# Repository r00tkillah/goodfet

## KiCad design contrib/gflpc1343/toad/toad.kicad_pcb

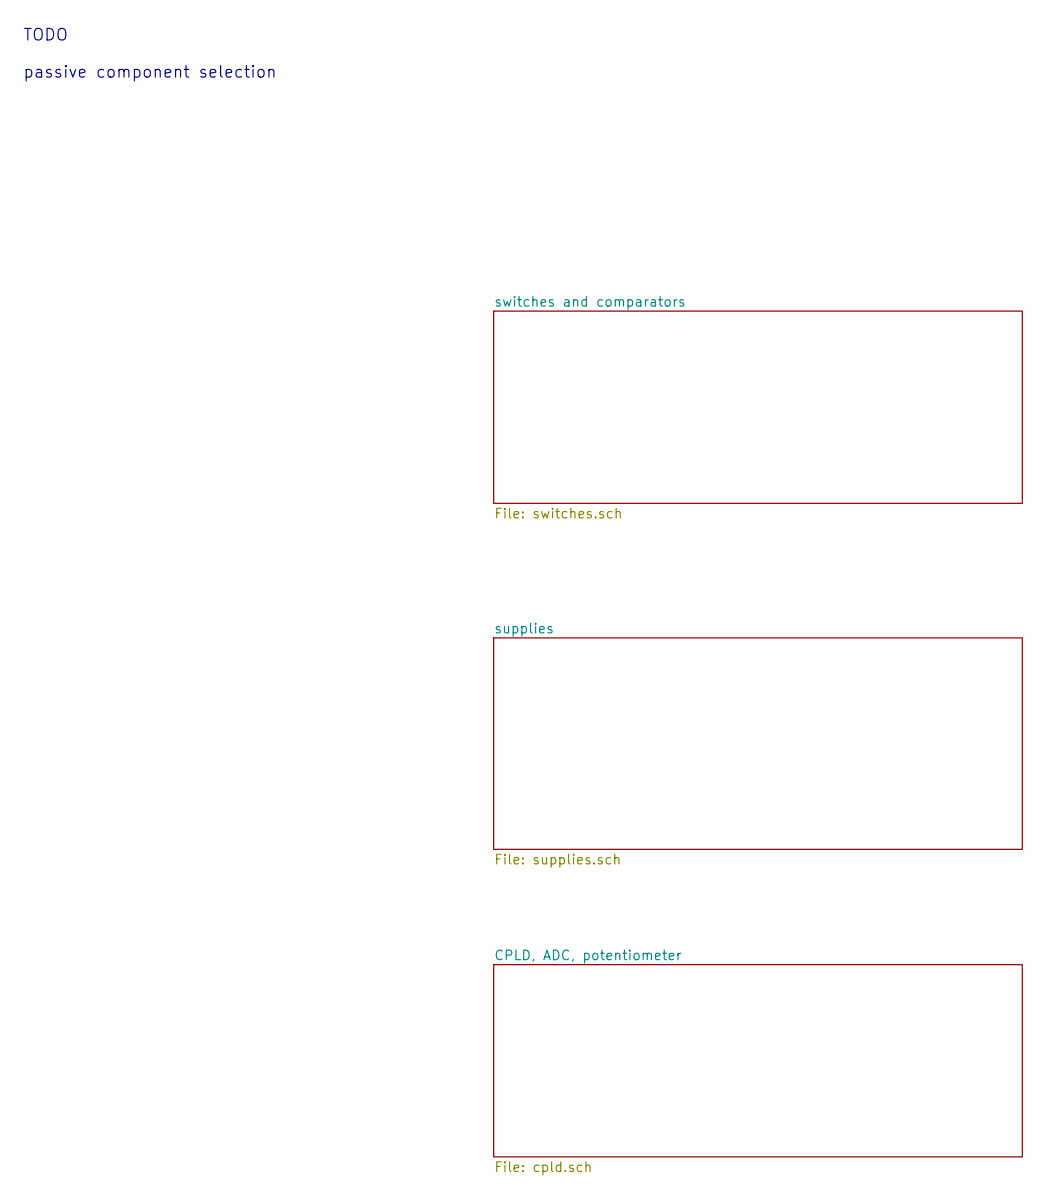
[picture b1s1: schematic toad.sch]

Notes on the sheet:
TODO passive component selection

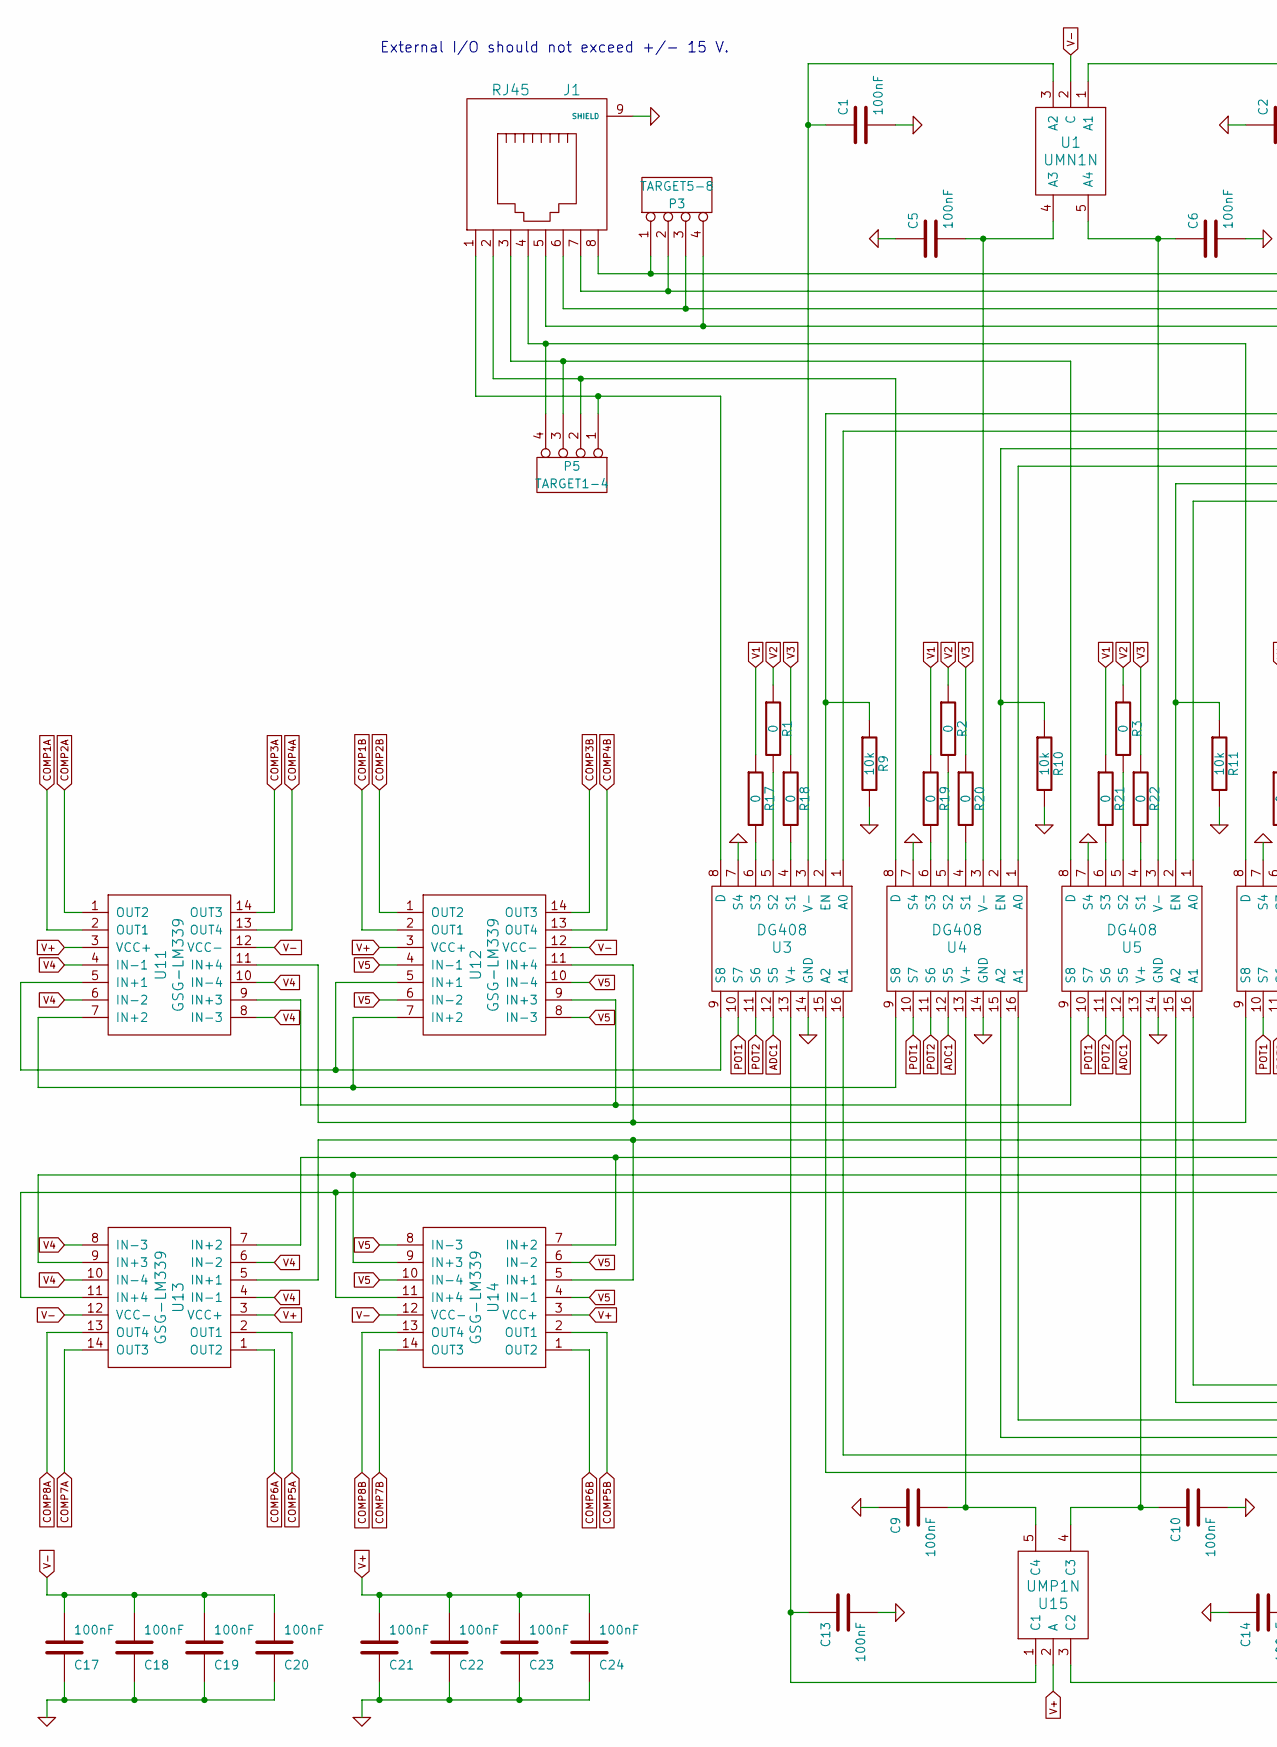
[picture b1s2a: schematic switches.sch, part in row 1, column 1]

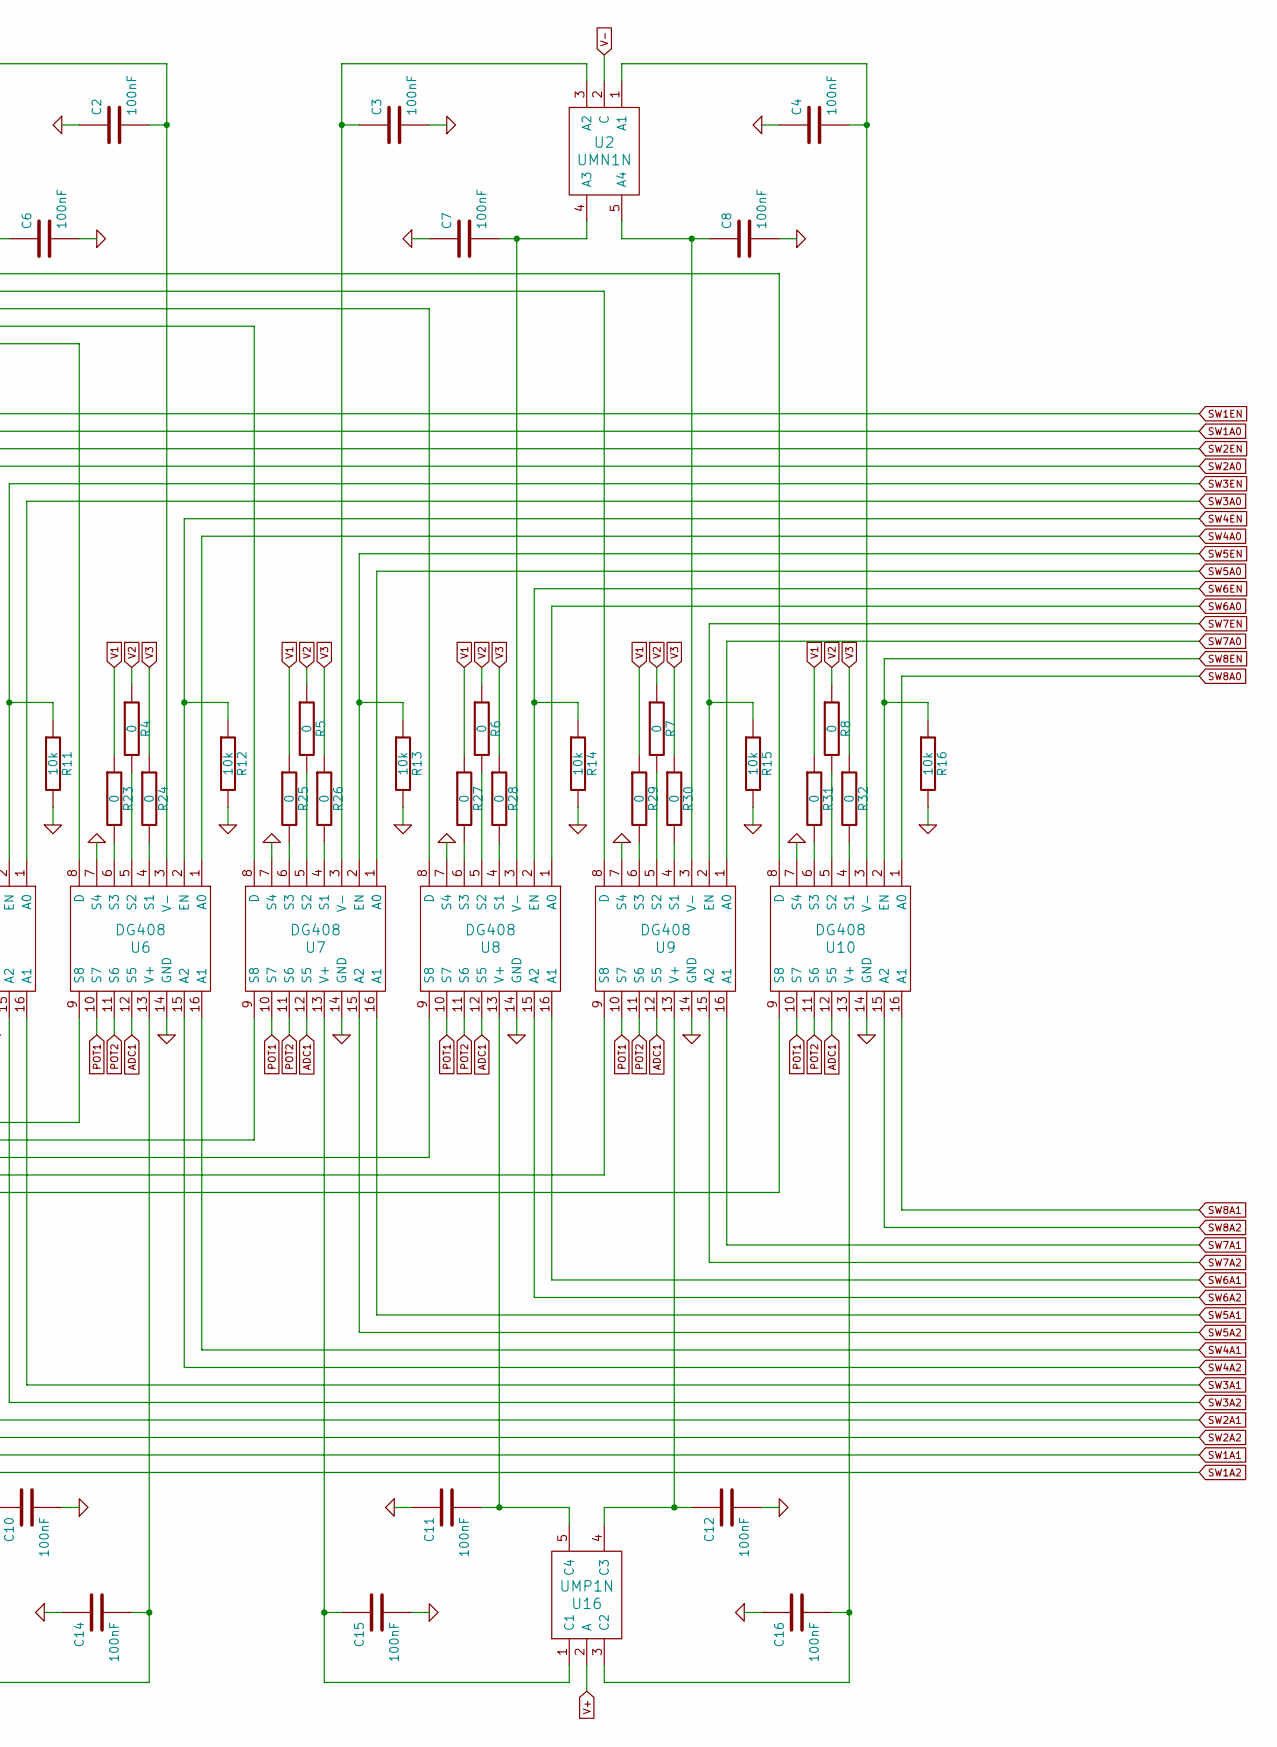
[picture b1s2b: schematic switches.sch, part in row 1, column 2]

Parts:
C1, C2, C3, C4, C5, C6, C7, C8, C9, C10, C11, C12, C13, C14, C15, C16, C17, C18, C19, C20, C21, C22, C23, C24: 100nF; Part Number CL10B104KB8SFNC
J1: RJ45
P3: TARGET5-8
P5: TARGET1-4
R1, R2, R3, R4, R5, R6, R7, R8, R17, R18, R19, R20, R21, R22, R23, R24, R25, R26, R27, R28, R29, R30, R31, R32: 0
R9, R10, R11, R12, R13, R14, R15, R16: 10k
U1, U2: UMN1N; Part Number UMN1NTR
U3, U4, U5, U6, U7, U8, U9, U10: DG408; Part Number DG408DQ-T1-E3
U11, U12, U13, U14: GSG-LM339; Part Number LM339PT
U15, U16: UMP1N; Part Number UMP1NTR

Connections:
ADC1: U3.12 (S5), U4.12 (S5), U5.12 (S5), U6.12 (S5), U7.12 (S5), U8.12 (S5), U9.12 (S5), U10.12 (S5); also elsewhere on the board
COMP1A: U11.2 (OUT1); also elsewhere on the board
COMP1B: U12.2 (OUT1); also elsewhere on the board
COMP2A: U11.1 (OUT2); also elsewhere on the board
COMP2B: U12.1 (OUT2); also elsewhere on the board
COMP3A: U11.14 (OUT3); also elsewhere on the board
COMP3B: U12.14 (OUT3); also elsewhere on the board
COMP4A: U11.13 (OUT4); also elsewhere on the board
COMP4B: U12.13 (OUT4); also elsewhere on the board
COMP5A: U13.2 (OUT1); also elsewhere on the board
COMP5B: U14.2 (OUT1); also elsewhere on the board
COMP6A: U13.1 (OUT2); also elsewhere on the board
COMP6B: U14.1 (OUT2); also elsewhere on the board
COMP7A: U13.14 (OUT3); also elsewhere on the board
COMP7B: U14.14 (OUT3); also elsewhere on the board
COMP8A: U13.13 (OUT4); also elsewhere on the board
COMP8B: U14.13 (OUT4); also elsewhere on the board
unnamed: U6.9 (S8), U11.11 (IN+4), U12.11 (IN+4)
unnamed: U4.9 (S8), U11.7 (IN+2), U12.7 (IN+2)
unnamed: U5.9 (S8), U11.9 (IN+3), U12.9 (IN+3)
unnamed: U9.9 (S8), U13.9 (IN+3), U14.9 (IN+3)
unnamed: U7.9 (S8), U13.5 (IN+1), U14.5 (IN+1)
unnamed: J1.6, P3.3, U8.8 (D)
unnamed: J1.1, P5.1, U3.8 (D)
unnamed: C16.2, U10.13 (V+), U16.3 (C2)
unnamed: C12.1, U9.13 (V+), U16.4 (C3)
unnamed: C14.2, U6.13 (V+), U15.3 (C2)
unnamed: C4.2, U2.1 (A1), U10.3 (V-)
unnamed: C8.1, U2.5 (A4), U9.3 (V-)
unnamed: C15.1, U7.13 (V+), U16.1 (C1)
unnamed: C11.2, U8.13 (V+), U16.5 (C4)
unnamed: C13.1, U3.13 (V+), U15.1 (C1)
unnamed: C5.2, U1.4 (A3), U4.3 (V-)
unnamed: R20.2, U4.4 (S1)
unnamed: R2.2, U4.5 (S2)
unnamed: C9.2, U4.13 (V+), U15.5 (C4)
unnamed: C6.1, U1.5 (A4), U5.3 (V-)
unnamed: R22.2, U5.4 (S1)
unnamed: R3.2, U5.5 (S2)
unnamed: C10.1, U5.13 (V+), U15.4 (C3)
unnamed: J1.5, P3.4, U7.8 (D)
unnamed: C7.2, U2.4 (A3), U8.3 (V-)
unnamed: R28.2, U8.4 (S1)
unnamed: R6.2, U8.5 (S2)
unnamed: R25.2, U7.6 (S3)
unnamed: U8.9 (S8), U13.7 (IN+2), U14.7 (IN+2)
unnamed: R30.2, U9.4 (S1)
unnamed: J1.3, P5.3, U5.8 (D)
unnamed: C2.2, U1.1 (A1), U6.3 (V-)
unnamed: C3.1, U2.3 (A2), U7.3 (V-)
unnamed: R26.2, U7.4 (S1)
unnamed: R5.2, U7.5 (S2)
unnamed: J1.4, P5.4, U6.8 (D)
unnamed: J1.2, P5.2, U4.8 (D)
unnamed: J1.8, P3.1, U10.8 (D)
unnamed: C1.1, U1.3 (A2), U3.3 (V-)
unnamed: R1.2, U3.5 (S2)
unnamed: U3.9 (S8), U11.5 (IN+1), U12.5 (IN+1)
unnamed: J1.7, P3.2, U9.8 (D)
unnamed: R7.2, U9.5 (S2)
unnamed: R4.2, U6.5 (S2)
unnamed: R24.2, U6.4 (S1)
unnamed: R21.2, U5.6 (S3)
unnamed: R19.2, U4.6 (S3)
unnamed: R27.2, U8.6 (S3)
unnamed: R23.2, U6.6 (S3)
unnamed: U10.9 (S8), U13.11 (IN+4), U14.11 (IN+4)
unnamed: R32.2, U10.4 (S1)
unnamed: R17.2, U3.6 (S3)
unnamed: R8.2, U10.5 (S2)
unnamed: R18.2, U3.4 (S1)
unnamed: R31.2, U10.6 (S3)
unnamed: R29.2, U9.6 (S3)
POT1: U3.10 (S7), U4.10 (S7), U5.10 (S7), U6.10 (S7), U7.10 (S7), U8.10 (S7), U9.10 (S7), U10.10 (S7); also elsewhere on the board
POT2: U3.11 (S6), U4.11 (S6), U5.11 (S6), U6.11 (S6), U7.11 (S6), U8.11 (S6), U9.11 (S6), U10.11 (S6); also elsewhere on the board
SW1A0: U3.1 (A0); also elsewhere on the board
SW1A1: U3.16 (A1); also elsewhere on the board
SW1A2: U3.15 (A2); also elsewhere on the board
SW1EN: R9.1, U3.2 (EN); also elsewhere on the board
SW2A0: U4.1 (A0); also elsewhere on the board
SW2A1: U4.16 (A1); also elsewhere on the board
SW2A2: U4.15 (A2); also elsewhere on the board
SW2EN: R10.1, U4.2 (EN); also elsewhere on the board
SW3A0: U5.1 (A0); also elsewhere on the board
SW3A1: U5.16 (A1); also elsewhere on the board
SW3A2: U5.15 (A2); also elsewhere on the board
SW3EN: R11.1, U5.2 (EN); also elsewhere on the board
SW4A0: U6.1 (A0); also elsewhere on the board
SW4A1: U6.16 (A1); also elsewhere on the board
SW4A2: U6.15 (A2); also elsewhere on the board
SW4EN: R12.1, U6.2 (EN); also elsewhere on the board
SW5A0: U7.1 (A0); also elsewhere on the board
SW5A1: U7.16 (A1); also elsewhere on the board
SW5A2: U7.15 (A2); also elsewhere on the board
SW5EN: R13.1, U7.2 (EN); also elsewhere on the board
SW6A0: U8.1 (A0); also elsewhere on the board
SW6A1: U8.16 (A1); also elsewhere on the board
SW6A2: U8.15 (A2); also elsewhere on the board
SW6EN: R14.1, U8.2 (EN); also elsewhere on the board
SW7A0: U9.1 (A0); also elsewhere on the board
SW7A1: U9.16 (A1); also elsewhere on the board
SW7A2: U9.15 (A2); also elsewhere on the board
SW7EN: R15.1, U9.2 (EN); also elsewhere on the board
SW8A0: U10.1 (A0); also elsewhere on the board
SW8A1: U10.16 (A1); also elsewhere on the board
SW8A2: U10.15 (A2); also elsewhere on the board
SW8EN: R16.1, U10.2 (EN); also elsewhere on the board
V1: R17.1, R19.1, R21.1, R23.1, R25.1, R27.1, R29.1, R31.1; also elsewhere on the board
V2: R1.1, R2.1, R3.1, R4.1, R5.1, R6.1, R7.1, R8.1; also elsewhere on the board
V3: R18.1, R20.1, R22.1, R24.1, R26.1, R28.1, R30.1, R32.1; also elsewhere on the board
V4: U11.4 (IN-1), U11.6 (IN-2), U11.8 (IN-3), U11.10 (IN-4), U13.4 (IN-1), U13.6 (IN-2), U13.8 (IN-3), U13.10 (IN-4); also elsewhere on the board
V5: U12.4 (IN-1), U12.6 (IN-2), U12.8 (IN-3), U12.10 (IN-4), U14.4 (IN-1), U14.6 (IN-2), U14.8 (IN-3), U14.10 (IN-4); also elsewhere on the board

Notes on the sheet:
External I/O should not exceed +/- 15 V.

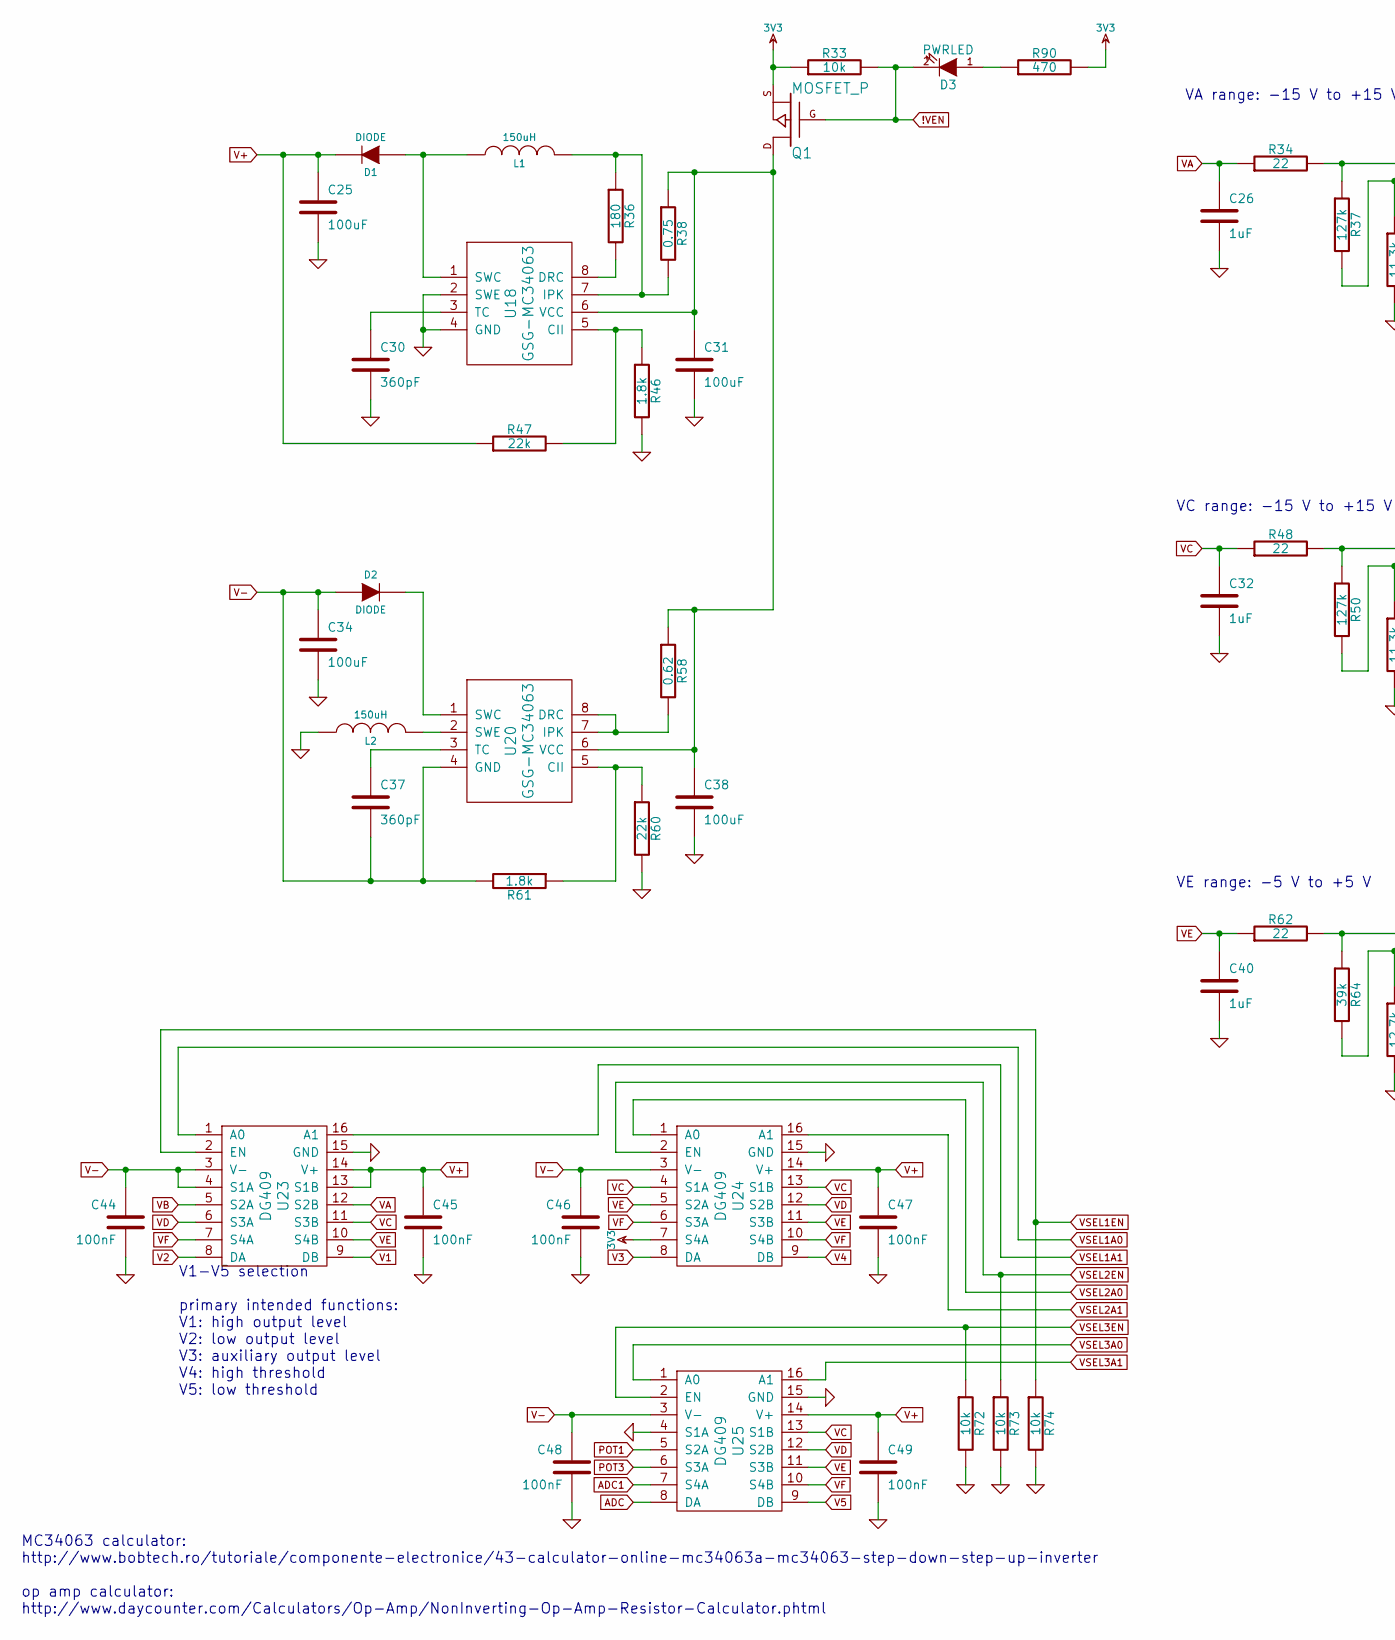
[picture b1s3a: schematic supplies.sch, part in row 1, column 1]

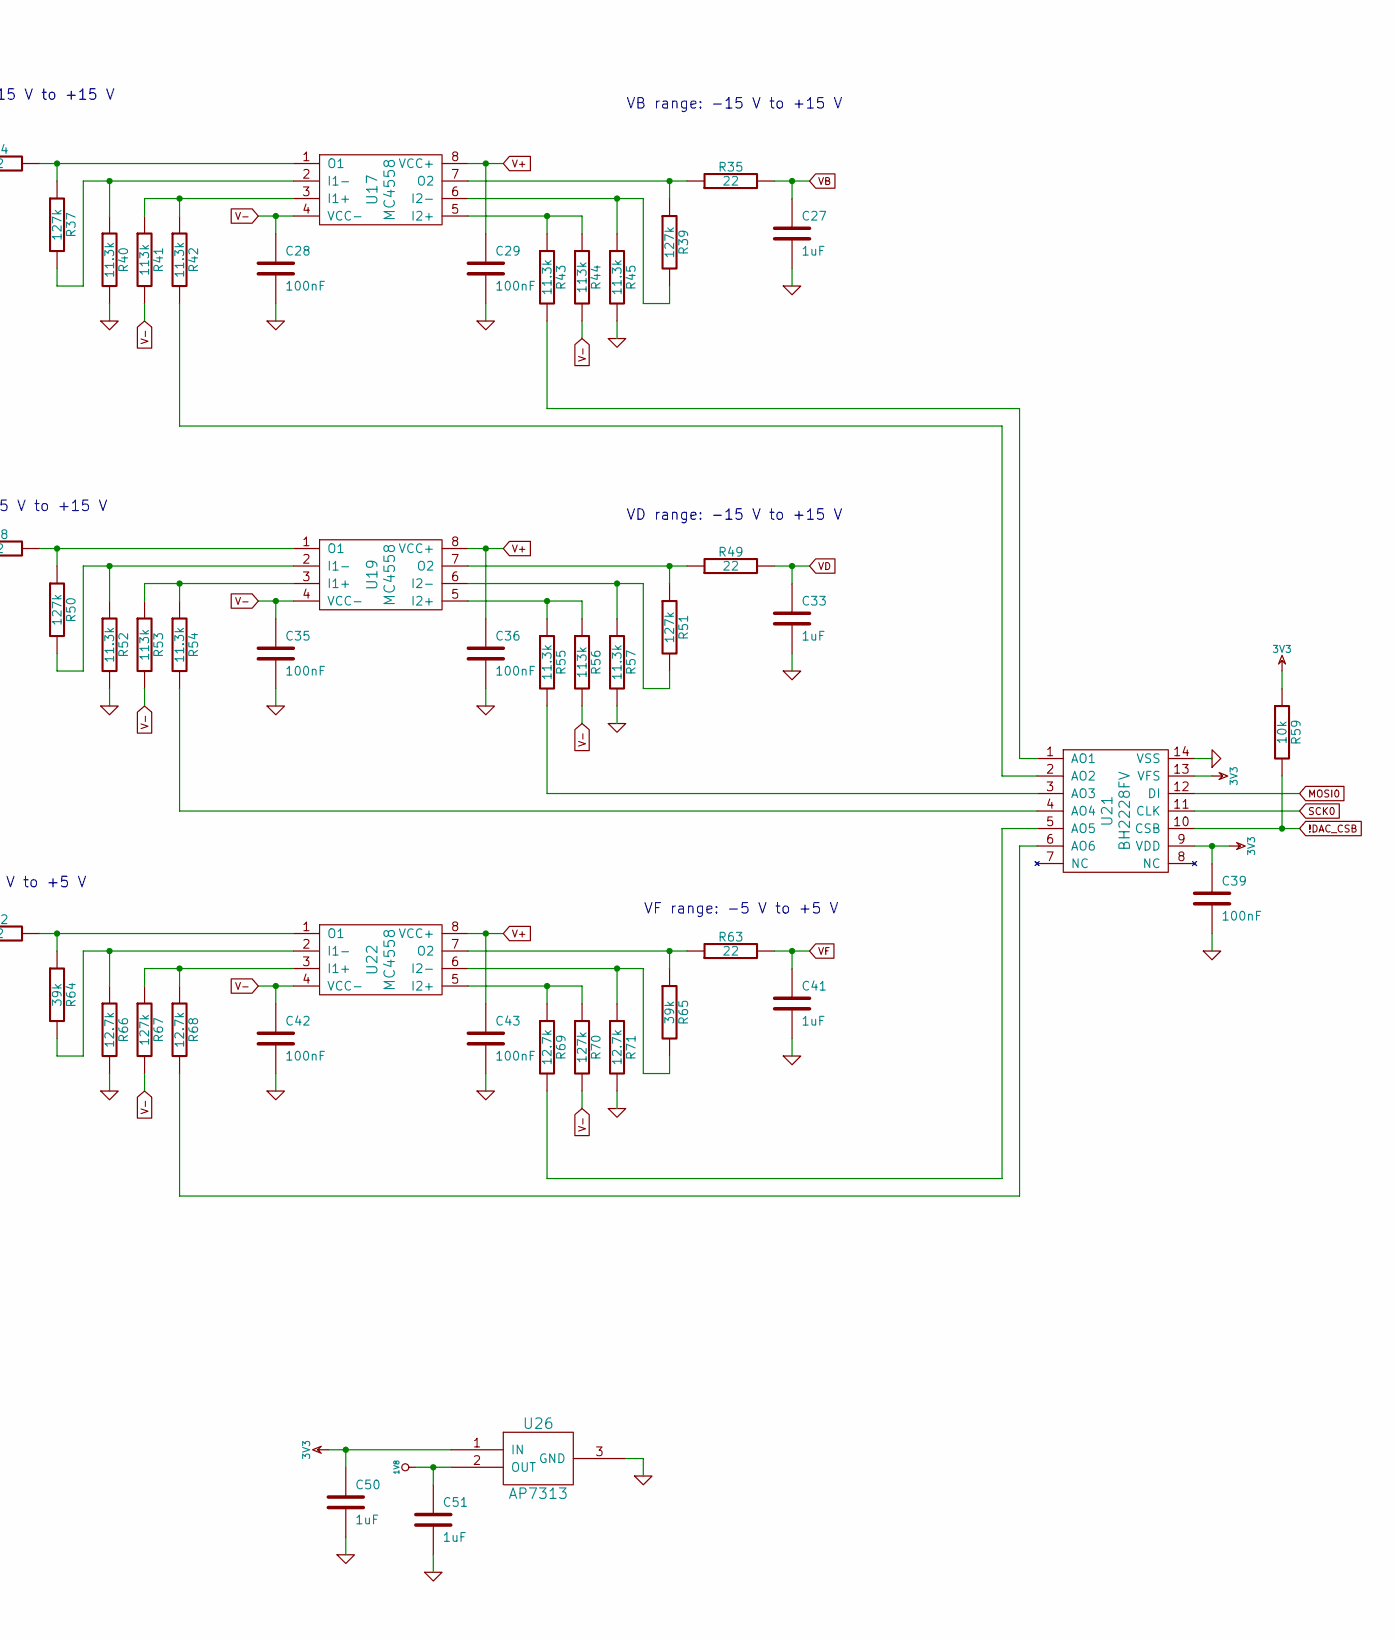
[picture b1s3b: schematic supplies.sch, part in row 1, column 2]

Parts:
C25, C31, C34, C38: 100uF; Part Number UWT1V101MCL1GS
C26, C27, C32, C33, C40, C41, C50, C51: 1uF; Part Number CL10A105KB8NNNC
C28, C29, C35, C36, C39, C42, C43, C44, C45, C46, C47, C48, C49: 100nF; Part Number CL10B104KB8SFNC
C30, C37: 360pF
D1, D2: DIODE; Part Number B140-13-F
D3: PWRLED
L1, L2: 150uH; Part Number SDR0603-151KL
Q1: MOSFET_P; Part Number DMP2100U-7
R33, R59, R72, R73, R74: 10k
R34, R35, R48, R49, R62, R63: 22; Part Number RC1608J220CS
R36: 180
R37, R39, R50, R51, R67, R70: 127k
R38: 0.75
R40, R42, R43, R45, R52, R54, R55, R57: 11.3k
R41, R44, R53, R56: 113k
R46, R61: 1.8k
R47, R60: 22k
R58: 0.62
R64, R65: 39k
R66, R68, R69, R71: 12.7k
R90: 470; Part Number RC1608J220CS
U17, U19, U22: MC4558; Part Number MC4558CPT
U18, U20: GSG-MC34063; Part Number MC34063ACD-TR
U21: BH2228FV; Part Number BH2228FV-E2
U23, U24, U25: DG409; Part Number DG409DQ-T1-E3
U26: AP7313; Part Number AP7313-18SAG-7

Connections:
3V3: C39.1, C50.1, Q1.S, R33.1, R59.1, R90.2, U21.9 (VDD), U21.13 (VFS), U24.7 (S4A), U26.1 (IN); also elsewhere on the board
!DAC_CSB: R59.2, U21.10 (CSB)
!VEN: D3.2 (K), Q1.G, R33.2; also elsewhere on the board
+1.8V: C51.1, U26.2 (OUT); also elsewhere on the board
ADC: U25.8 (DA); also elsewhere on the board
ADC1: U25.7 (S4A); also elsewhere on the board
MOSI0: U21.12 (DI); also elsewhere on the board
unnamed: R69.2, U21.5 (AO5)
unnamed: R68.2, U21.6 (AO6)
unnamed: R42.2, U21.2 (AO2)
unnamed: R43.2, U21.1 (AO1)
unnamed: R67.1, R68.1, U22.3 (I1+)
unnamed: R64.2, R66.1, U22.2 (I1-)
unnamed: R69.1, R70.1, U22.5 (I2+)
unnamed: R65.2, R71.1, U22.6 (I2-)
unnamed: R63.1, R65.1, U22.7 (O2)
unnamed: R39.2, R45.1, U17.6 (I2-)
unnamed: R35.1, R39.1, U17.7 (O2)
unnamed: R37.2, R40.1, U17.2 (I1-)
unnamed: R34.2, R37.1, U17.1 (O1)
unnamed: R41.1, R42.1, U17.3 (I1+)
unnamed: R43.1, R44.1, U17.5 (I2+)
unnamed: R49.1, R51.1, U19.7 (O2)
unnamed: R62.2, R64.1, U22.1 (O1)
unnamed: R55.1, R56.1, U19.5 (I2+)
unnamed: R48.2, R50.1, U19.1 (O1)
unnamed: R53.1, R54.1, U19.3 (I1+)
unnamed: R50.2, R52.1, U19.2 (I1-)
unnamed: R51.2, R57.1, U19.6 (I2-)
unnamed: D3.1 (A), R90.1
unnamed: C37.1, U20.3 (TC)
unnamed: R55.2, U21.3 (AO3)
unnamed: R54.2, U21.4 (AO4)
unnamed: R46.1, R47.2, U18.5 (CII)
unnamed: R60.1, R61.1, U20.5 (CII)
unnamed: C30.1, U18.3 (TC)
unnamed: R36.2, U18.8 (DRC)
unnamed: L1.2, R36.1, R38.2, U18.7 (IPK)
unnamed: C31.1, C38.1, Q1.D, R38.1, R58.1, U18.6 (VCC), U20.6 (VCC)
POT1: U25.5 (S2A); also elsewhere on the board
POT3: U25.6 (S3A); also elsewhere on the board
SCK0: U21.11 (CLK); also elsewhere on the board
V1: U23.9 (DB); also elsewhere on the board
V2: U23.8 (DA); also elsewhere on the board
V3: U24.8 (DA); also elsewhere on the board
V4: U24.9 (DB); also elsewhere on the board
V5: U25.9 (DB); also elsewhere on the board
VA: C26.1, R34.1, U23.12 (S2B)
VB: C27.1, R35.2, U23.5 (S2A)
VC: C32.1, R48.1, U23.11 (S3B), U24.4 (S1A), U24.13 (S1B), U25.13 (S1B); also elsewhere on the board
VD: C33.1, R49.2, U23.6 (S3A), U24.12 (S2B), U25.12 (S2B); also elsewhere on the board
VE: C40.1, R62.1, U23.10 (S4B), U24.5 (S2A), U24.11 (S3B), U25.11 (S3B); also elsewhere on the board
VF: C41.1, R63.2, U23.7 (S4A), U24.6 (S3A), U24.10 (S4B), U25.10 (S4B); also elsewhere on the board
VSEL1A0: U23.1 (A0); also elsewhere on the board
VSEL1A1: U23.16 (A1); also elsewhere on the board
VSEL1EN: R74.1, U23.2 (EN); also elsewhere on the board
VSEL2A0: U24.1 (A0); also elsewhere on the board
VSEL2A1: U24.16 (A1); also elsewhere on the board
VSEL2EN: R73.1, U24.2 (EN); also elsewhere on the board
VSEL3A0: U25.1 (A0); also elsewhere on the board
VSEL3A1: U25.16 (A1); also elsewhere on the board
VSEL3EN: R72.1, U25.2 (EN); also elsewhere on the board

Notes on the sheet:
VA range: -15 V to +15 V
VB range: -15 V to +15 V
VC range: -15 V to +15 V
VD range: -15 V to +15 V
VE range: -5 V to +5 V
VF range: -5 V to +5 V
MC34063 calculator: http://www.bobtech.ro/tutoriale/componente-electronice/43-calculator-online-mc34063a-mc34063-step-down-step-up-inverter op amp calculator: http://www.daycounter.com/Calculators/Op-Amp/NonInverting-Op-Amp-Resistor-Calculator.phtml
V1-V5 selection primary intended functions: V1: high output level V2: low output level V3: auxiliary output level V4: high threshold V5: low threshold
